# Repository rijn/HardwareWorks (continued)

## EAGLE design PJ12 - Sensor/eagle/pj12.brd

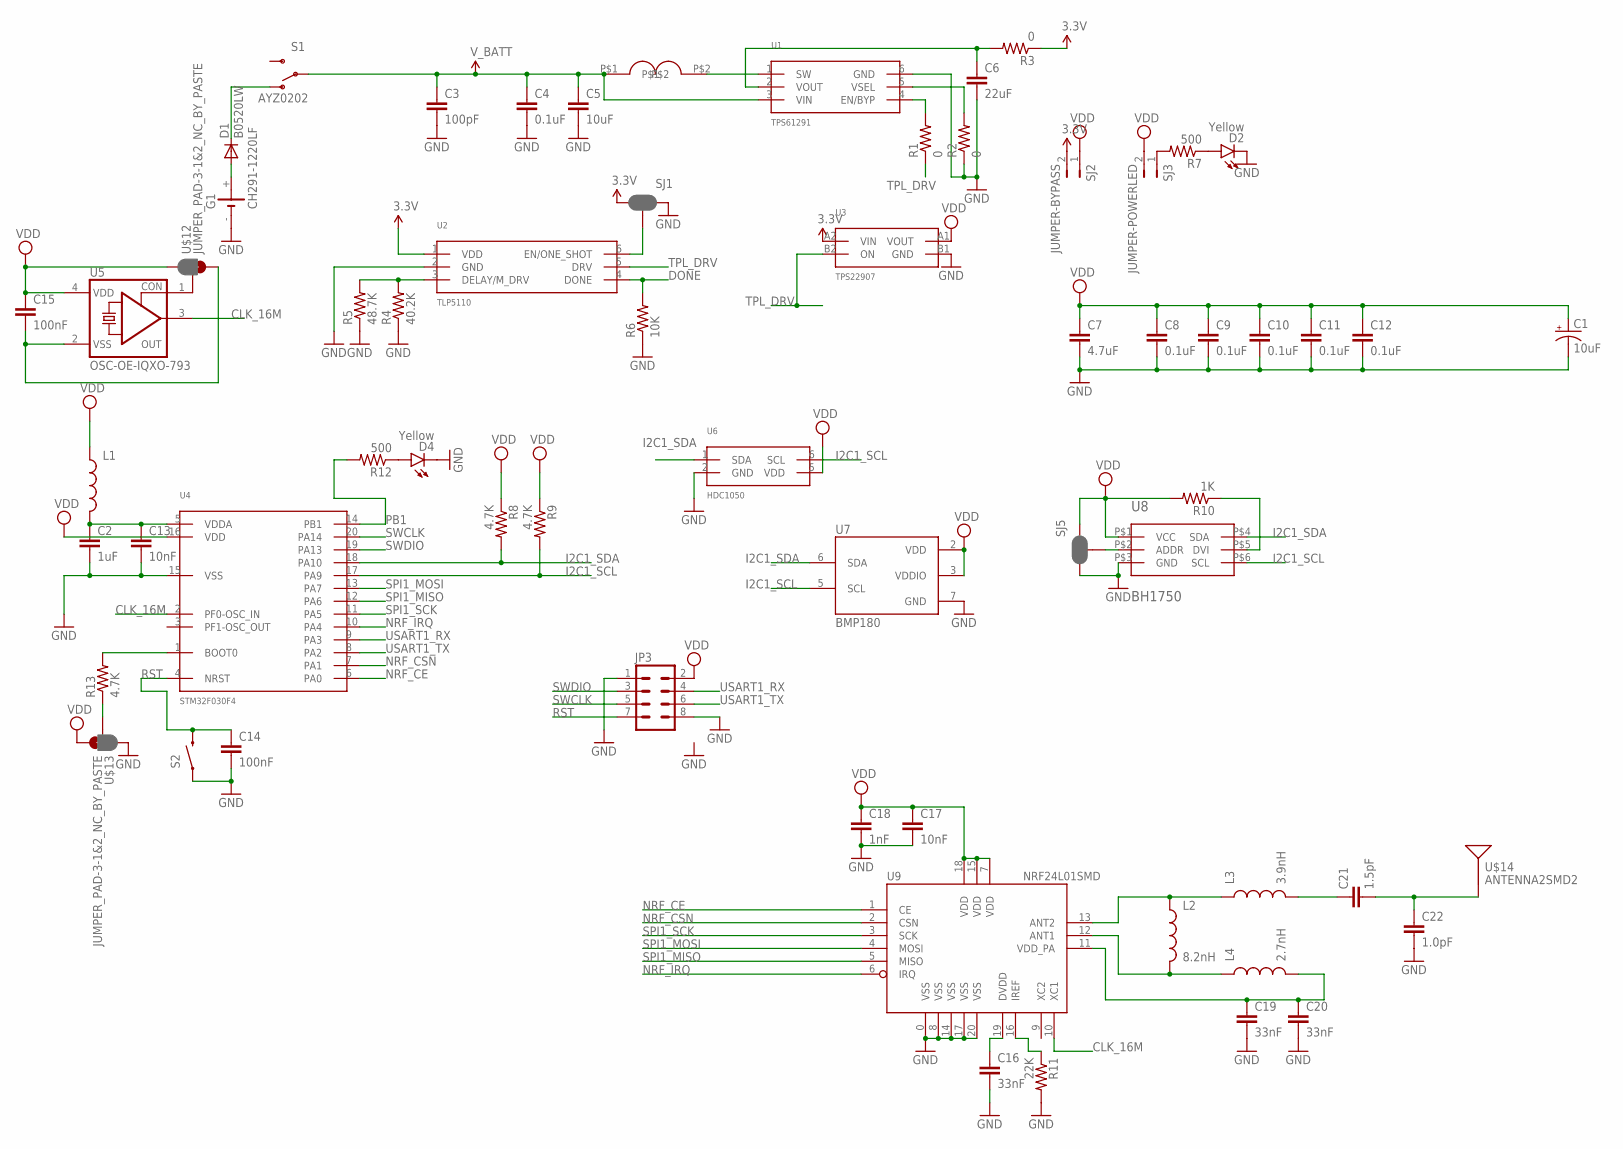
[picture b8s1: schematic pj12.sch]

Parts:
C1: 10uF; EIA3216
C2: 1uF; 0603-CAP
C3: 100pF; 0603-CAP
C4, C8, C9, C10, C11, C12: 0.1uF; 0603-CAP
C5: 10uF; 0603-CAP
C6: 22uF; 0603-CAP
C7: 4.7uF; 0603-CAP
C13, C17: 10nF; 0603-CAP
C14, C15: 100nF; 0603-CAP
C16, C19, C20: 33nF; 0603-CAP
C18: 1nF; 0603-CAP
C21: 1.5pF; 0603-CAP
C22: 1.0pF; 0603-CAP
D1: B0520LW; SOD-123_MINI-SMA
D2, D4: Yellow; LED-0603
G1: CH291-1220LF
JP3: M04X2SMD; 2X4_SMD
L1: INDUCTOR0603; 0603
L2: 8.2nH; 0603
L3: 3.9nH; 0603
L4: 2.7nH; 0603
R1, R2, R3: 0; 0603
R4: 40.2K; 0805
R5: 48.7K; 0805
R6: 10K; 0603
R7, R12: 500; 0603
R8, R9, R13: 4.7K; 0603
R10: 1K; 0603
R11: 22K; 0603
S1: AYZ0202
S2: SWITCH-MOMENTARY-2SMD-REDUNDANT; TACTILE-SWITCH-SMD
SJ1, SJ5: JUMPER-PAD-3-NC_BY_PASTE; PAD-JUMPER-3-NC_BY_PASTE_YES_SILK_FULL_BOX
SJ2: JUMPER-BYPASS; PTH-JUMPER-2-NO_NO_SILK
SJ3: JUMPER-POWERLED; PTH-JUMPER-2-NO_NO_SILK
U1: TPS61291; DRV(S-PWSON-N6)
U2: TLP5110; DDC(R-PDSO-G6)
U3: TPS22907; YZT(S-XBGA-N4)
U4: STM32F030F4; TSSOP20
U5: OSC-OE-IQXO-793; 2.5X2-4-PAD
U6: HDC1050; DMB(S-PWSON-N6)
U7: BMP180
U8: BH1750; WSOF-6
U9: NRF24L01SMD; QFN20
U$1: SWPA4018S3R3MT; SWPA4018S
U$12, U$13: JUMPER_PAD-3-1&2_NC_BY_PASTE; PAD-HUMPER-3-1&2_NC_BY_PASTE_YES_SILK_FULL_BOX
U$14: ANTENNA2SMD2; ANTENNA-CHIP3

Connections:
3.3V: R3.1, SJ1.1, SJ2.2, U2.1 (VDD), U3.A2 (VIN)
CLK_16M: U4.2 (PF0-OSC_IN), U5.3 (OUT), U9.10 (XC1)
DONE: R6.2, U2.4 (DONE)
GND: C1.C (-), C2.2, C3.2, C4.2, C5.2, C6.2, C7.2, C8.2, C9.2, C10.2, C11.2, C12.2, C13.2, C14.2, C16.2, C17.2, C18.2, C19.2, C20.2, C22.2, D2.C, D4.C, G1.-, JP3.1, JP3.8, R2.1, R4.1, R5.1, R6.1, R11.2, S2.1, S2.2 (1), SJ1.3, SJ5.1, U1.6 (GND), U2.2 (GND), U3.B1 (GND), U4.15 (VSS), U6.2 (GND), U7.7 (GND), U8.P$3 (GND), U9.0 (VSS), U9.8 (VSS), U9.14 (VSS), U9.17 (VSS), U9.20 (VSS), U$13.1
I2C1_SCL: R9.2, U4.17 (PA9), U6.6 (SCL), U7.5 (SCL), U8.P$6 (SCL)
I2C1_SDA: R8.2, U4.18 (PA10), U6.1 (SDA), U7.6 (SDA), U8.P$4 (SDA)
unnamed: D1.A, G1.+
unnamed: D1.C, S1.1 (O)
unnamed: U1.1 (SW), U$1.P$2
unnamed: C6.1, R3.2, U1.2 (VOUT)
unnamed: R1.2, U1.4 (EN/BYP)
unnamed: R2.2, U1.5 (VSEL)
unnamed: R4.2, R5.2, U2.3 (DELAY/M_DRV)
unnamed: R7.2, SJ3.1
unnamed: D2.A, R7.1
unnamed: SJ1.2, U2.6 (EN/ONE_SHOT)
unnamed: L2.1, L3.1, U9.13 (ANT2)
unnamed: SJ5.2, U8.P$2 (ADDR)
unnamed: R10.1, U8.P$5 (DVI)
unnamed: L2.2, L4.1, U9.12 (ANT1)
unnamed: D4.A, R12.1
unnamed: C15.2, U5.2 (VSS), U$12.3
unnamed: C2.1, C13.1, L1.2, U4.5 (VDDA)
unnamed: C19.1, C20.1, L4.2, U9.11 (VDD_PA)
unnamed: R13.1, U$13.2
unnamed: R13.2, U4.1 (BOOT0)
unnamed: U5.1 (CON), U$12.2
unnamed: C16.1, U9.19 (DVDD)
unnamed: R11.1, U9.16 (IREF)
unnamed: C21.1, L3.2
unnamed: C21.2, C22.1, U$14.FEED
NRF_CE: U4.6 (PA0), U9.1 (CE)
NRF_CSN: U4.7 (PA1), U9.2 (CSN)
NRF_IRQ: U4.10 (PA4), U9.6 (IRQ)
PB1: R12.2, U4.14 (PB1)
RST: C14.1, JP3.7, S2.3 (2), S2.4 (2), U4.4 (NRST)
SPI1_MISO: U4.12 (PA6), U9.5 (MISO)
SPI1_MOSI: U4.13 (PA7), U9.4 (MOSI)
SPI1_SCK: U4.11 (PA5), U9.3 (SCK)
SWCLK: JP3.5, U4.20 (PA14)
SWDIO: JP3.3, U4.19 (PA13)
TPL_DRV: R1.1, U2.5 (DRV), U3.B2 (ON)
USART1_RX: JP3.4, U4.9 (PA3)
USART1_TX: JP3.6, U4.8 (PA2)
VDD: C1.A (+), C7.1, C8.1, C9.1, C10.1, C11.1, C12.1, C15.1, C17.1, C18.1, JP3.2, L1.1, R8.1, R9.1, R10.2, SJ2.1, SJ3.2, SJ5.3, U3.A1 (VOUT), U4.16 (VDD), U5.4 (VDD), U6.5 (VDD), U7.2 (VDD), U7.3 (VDDIO), U8.P$1 (VCC), U9.7 (VDD), U9.15 (VDD), U9.18 (VDD), U$12.1, U$13.3
V_BATT: C3.1, C4.1, C5.1, S1.2, U1.3 (VIN), U$1.P$1

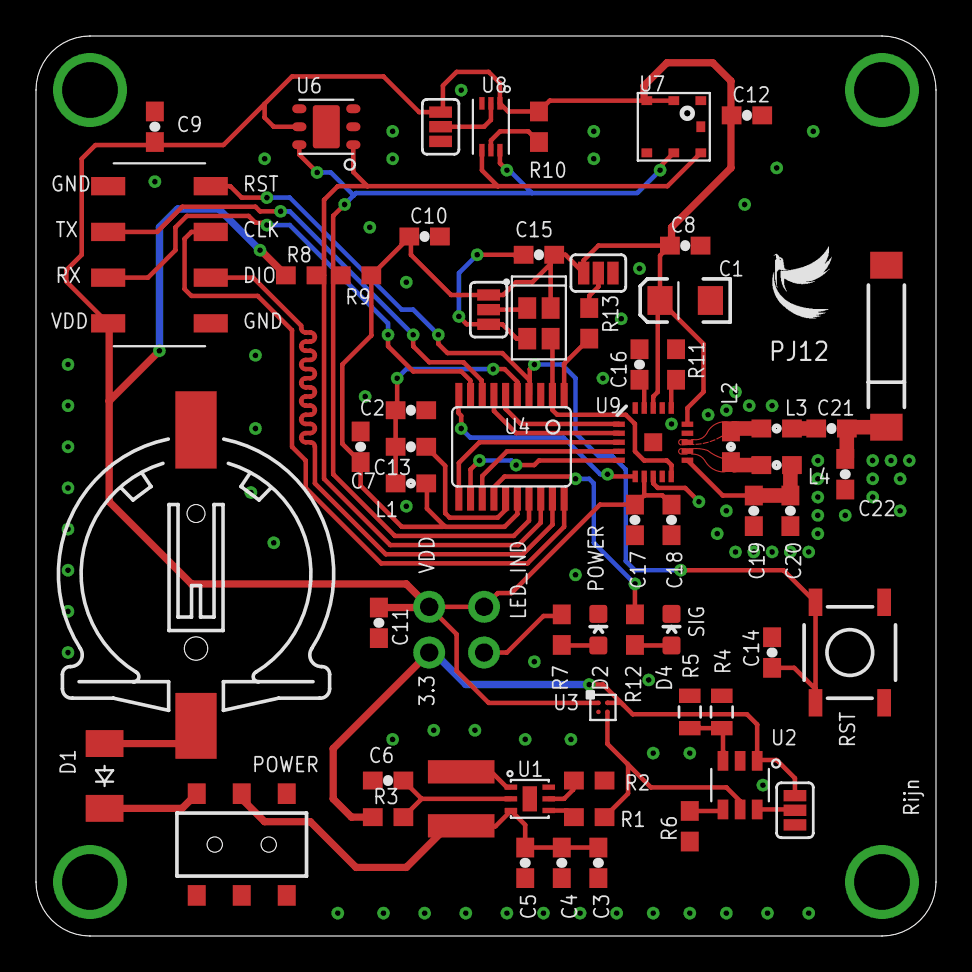
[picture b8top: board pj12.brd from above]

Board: 2 copper layers, 50.0 x 50.0 mm, 65 parts (1 on the bottom side), 46 nets.

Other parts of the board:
U$2: ESD_10.00
U$3: LOGO
